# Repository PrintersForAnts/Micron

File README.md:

## Micron R1

# [Printed Part Configurator](https://micron.wizards-enclave.net/) 
<p align="center">
   &nbsp;
   &nbsp;
   &nbsp;
   &nbsp;
  <a aria-label="Discord" href="">

</p>

[The official Micron BOM is here.](https://docs.google.com/spreadsheets/d/1caKSc-EukVpRgN67_by_hdzVPlExSRQ66j3OXlEmcCU)

If you want to purchase full kits there are 3 available (Kits are slowly updating to R1 hardware just make sure to double check the included hardware in your kit and if you have any questions reach out in the discord) 

## LDO Motors Kit 
### US Vendors
[Fabreeko](https://www.fabreeko.com/products/ldo-micron-3d-printer-kit-180mm-3d-printer-kit-with-honeybadger-upgrades)

[KB3D](https://kb-3d.com/store/shop-full-build-kits/6567-ldo-micron-r1-3d-printer-build-kit-by-hartk-6975415159954.html)

[West3d](https://west3d.com/products/ldo-micron-3d-printer-kit-micron-plus-180?_pos=1&_sid=03fbc1c81&_ss=r)

### Non US Vendors

[onetwo3d](https://www.onetwo3d.co.uk/product/ldo-micron-r1-diy-kit/?srsltid=AfmBOoraRNvGTTXXeaEX4yjF97ePEQ5GCPq-xmhn3iUpy0nTGUWonMrJ)

[Zen3d](https://shop.zen3d.eu/ldo-micronplus-r1-kit-black)

## Formbot 3d Kit 
<a href="https://www.formbot3d.com/products/voron-micron-r1-180mm-high-quality-corexy-3d-printer-kit-latest-version?DIST=Rk9OHl4%3D" rel="nofollow">Formbot Micron+ (180x180) Kit (Affiliate Link)</a>

<a href="https://s.click.aliexpress.com/e/_DBn6Ptd" rel="sponsored">Funssor Micron (120x120) Kit (Affiliate Link)</a>

<a href="https://s.click.aliexpress.com/e/_DDDUFkF" rel="nofollow">Formbot Micron+ (180x180) Kit (Aliexpress Affiliate Link)</a>

## [R1 Change Log](https://github.com/PrintersForAnts/Micron/blob/main/R1_changeLog.md)

<details> 
   <summary>
    120x120 build
    </summary>

## Frame Extrusions
Misumi Part #  |Qty | Notes
 ----|----|----|
HFS3-1515-300 |4 | Blind holes need to be drilled
HFS3-1515-220 |10| Ends need to be tapped (M3)
HFS3-1515-205 |2 |
HFS3-1515-190 |1 |
HFS3-1515-120 |1 |

## Linear Rails
Part  | Qty | Length | Notes
-----|----|----|----|
MGN7H | 6 | 160mm | will work with V0 150mm rails if wanted, but 160mm will work as well and is recommended  
MGN9C OR MGN9H | 1 | 160mm | will work V0 150mm rails but 160 will work as well and is recommended 
</details>

<details>
    <summary>
    180x180 build
    </summary>
    
## Frame Extrusions
Misumi Part #  |Qty | Notes
 ----|----|----|
HFS3-1515-350 |4 | Blind holes need to be drilled
HFS3-1515-280 |10| Ends need to be tapped (M3)
HFS3-1515-265 |2 |
HFS3-1515-250 |1 |
HFS3-1515-180 |1 |

## Linear Rails
Part  | Qty | Length
-----|-----|-----|
MGN7H | 6 | 220mm
MGN9C OR MGN9H | 1 | 220mm 
</details>

## No Drop Nuts
There are 2 versions of this mod, 1 from [Zruncho](https://github.com/VoronDesign/VoronUsers/tree/master/printer_mods/zruncho/V0_No_Drop_Nuts) and the other from a user named [Zen3D](https://github.com/VoronDesign/VoronUsers/tree/master/printer_mods/Zen3D/V0_1515_T-nut/). Both of them have their uses. I prefer to use the Zen3D kind just for the fact that the screw can go all the way through the printed part. Zrunchos do have a much nicer fitment into the extrusions but they also dont allow the screw to go all the way through. **NOTE:** the Zruncho nuts will not fit anywhere that has a tab to index to the extrusion - this includes the A/B drives, all idlers, and skirts. If you want to print only one type of nut, use the Zen3d nuts.

## Thank you
Thanks to the following people on Discord who have helped make this printer what it is today. 

- [@KyleGB](https://github.com/Jadecky) - too many additions to name them all
- @TheWarolf#1247
- @L.e.o.p.a.r.d#0990
- @deepfriedheroin#5006
- @JosAr#0517
- @sentein#3903
- @madcat#7838
- @Kyrios#5486
- @faithblinded#1491
- @zruncho#1790
- @Finn#2449
- @clee#1337
- @slidr#4412
- @gfunnymoney#3748
- Jason from LDO
- Voron Dev Team
- all the R1 beta testers
  
[You can support the Micron project on Patreon](https://www.patreon.com/user?u=27661824&fan_landing=true).

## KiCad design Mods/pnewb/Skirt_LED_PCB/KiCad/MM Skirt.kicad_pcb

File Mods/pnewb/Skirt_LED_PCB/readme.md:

# Micron Skirt LEDs #

# Disclaimer #
 This is baby's first PCB.  I have no clue what I'm doing, and take no responsibility if things go pear shaped.  That being said, the KiCad is all in the KiCad folder, along with a zip of the Gerbers that you'd drop onto JLCPCB to make an order.  
 
 Also they're made with the WS2812B-V5 in mind.  These have the decoupling capacitors built in.  If you use the standard issue, probably it'll be fine, maybe a light glitches every now and again, or maybe the first in the chain dies sooner.  Dunno.  As stated above, I have no idea what I'm doing.  `Lab_in_a_lab_coat.jpg`.

Insert the Diffuser and Light blocker into the main body

Slide the PCB in the grooves along the edge

# Sample Config # 
This assumes you're using the optional pass-through to chain from one board into the second.

    [neopixel Skirt_LEDs]
    pin:RGB_PIN
    chain_count: 16
    color_order: GRB
    initial_RED:0.6
    initial_GREEN: 0.6
    initial_BLUE: 0.6

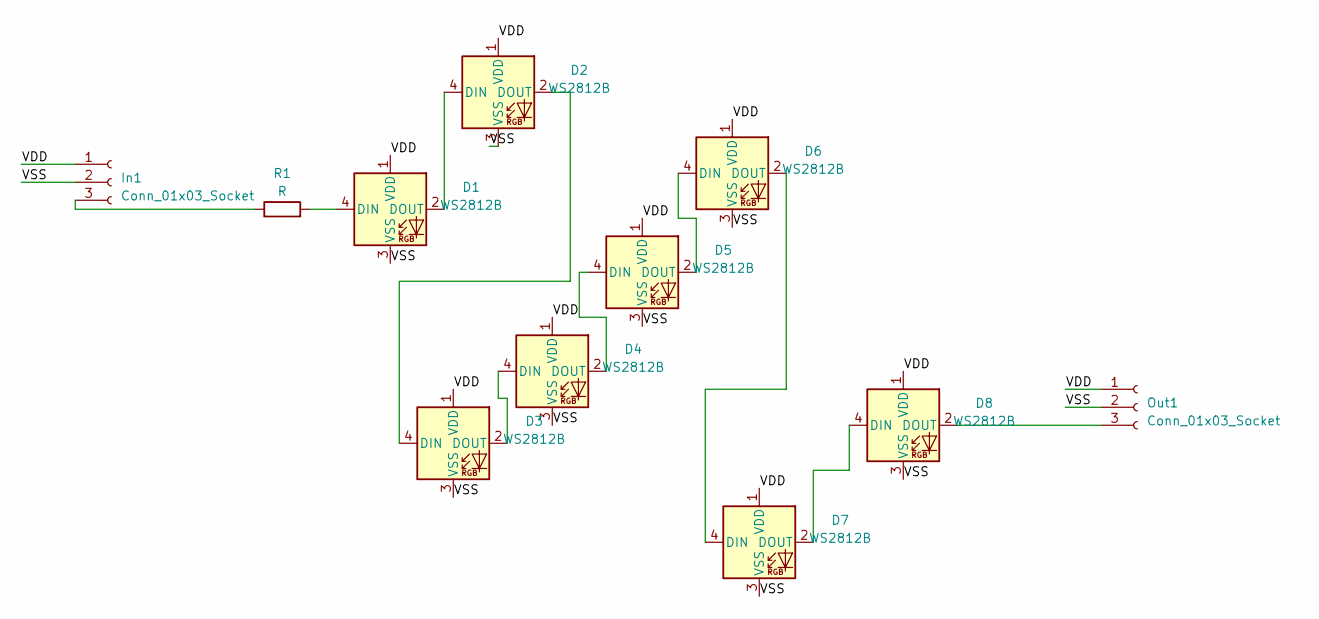
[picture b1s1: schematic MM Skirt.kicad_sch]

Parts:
D1, D2, D3, D4, D5, D6, D7, D8: WS2812B; LED_WS2812B_PLCC4_5.0x5.0mm_P3.2mm
In1: Conn_01x03_Socket; JST_XH_B3B-XH-A_1x03_P2.50mm_Vertical
Out1: Conn_01x03_Socket; JST_XH_B3B-XH-A_1x03_P2.50mm_Vertical
R1: R; R_1206_3216Metric

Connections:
/VDD: D1.1 (VDD), D2.1 (VDD), D3.1 (VDD), D4.1 (VDD), D5.1 (VDD), D6.1 (VDD), D7.1 (VDD), D8.1 (VDD), In1.1, Out1.1
/VSS: D1.3 (VSS), D2.3 (VSS), D3.3 (VSS), D4.3 (VSS), D5.3 (VSS), D6.3 (VSS), D7.3 (VSS), D8.3 (VSS), In1.2, Out1.2
unnamed: D1.4 (DIN), R1.2
unnamed: D1.2 (DOUT), D2.4 (DIN)
unnamed: D2.2 (DOUT), D3.4 (DIN)
unnamed: D3.2 (DOUT), D4.4 (DIN)
unnamed: D4.2 (DOUT), D5.4 (DIN)
unnamed: D5.2 (DOUT), D6.4 (DIN)
unnamed: D6.2 (DOUT), D7.4 (DIN)
unnamed: D7.2 (DOUT), D8.4 (DIN)
unnamed: D8.2 (DOUT), Out1.3
unnamed: In1.3, R1.1

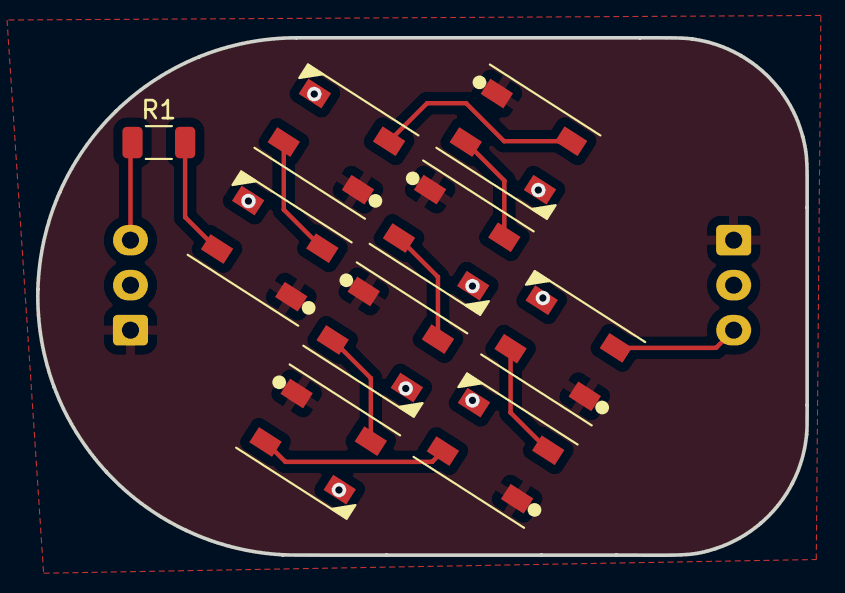
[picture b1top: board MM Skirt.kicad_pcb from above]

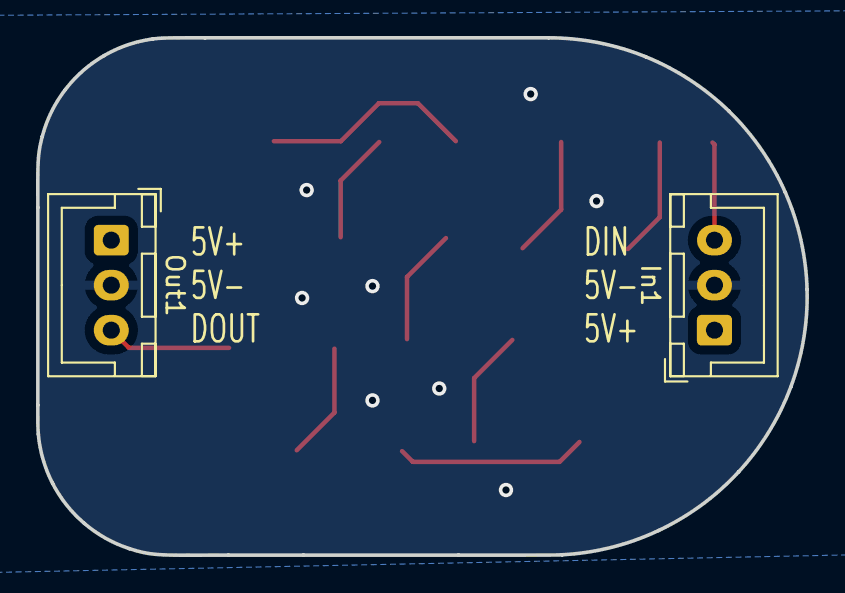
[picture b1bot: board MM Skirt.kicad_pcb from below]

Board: 2 copper layers, 42.7 x 28.7 mm, 11 parts (2 on the bottom side), 12 nets.

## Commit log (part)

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2022-12-18 Delete Mods/clee/Micron+/STLs directory
    no longer needed
2023-01-08 added miniSB, moved miniAB to its own folder
2023-01-08 Re uploading this as it somehow got deleted
2023-01-09 orientation fixed
2023-01-10 updated assembly with miniSB
2023-01-25 updated rail stops to be thicker to fit m3x8s better
2023-03-01 added new render , added cad for slotted fan skirts, updated the fan grills
2023-03-03 updated CAD assembly and fixed naming of some of the STLs
2023-03-18 new gantry , fixed minor alignment issues
2023-03-20 organized waveshare / slotted skirts mod
2023-03-24 updated XY joints belt alignment issues, added alignment tabs on extra a drive upper frame pieces
    fixes issue https://github.com/PrintersForAnts/Micron/issues/89
2023-03-26 updated pin mod for newest gantry fix
2023-03-27 updated XY joints and front idlers
2023-03-27 fixed a drive uppers and orientation on b drive lower pinned
2023-05-01 Various updates
    fixed the alignment of the Z drive gt2 16pulley (moved it over 1.2mm) and adjusted printed spacers to match (3.4mm change to 4.6mm, and 2.2mm change to 1mm)
    fixed the screw holes in the XY Joints Lower Left and Right
    added updated CAD assembly in both .F3D and .Step
2023-05-04 latest fix for XY joints to move bearings in and get belt aligned properly
2023-05-19 fixed probe mount to work with m3x16s better, added z drive spacers for different pulley setups
2023-05-27 organized my mods
2023-05-27 updated pin xy left lower joint
2023-05-31 update before making PR to main branch
2023-06-05 handles added to main cad assembly and stls
2023-06-05 fixed hole size for stepper mounting on lower A and B drive
2023-07-07 Added Bed Fan Mount for Micon+
2023-07-07 Add thumbnail for CAD/PFA_MiniSB_Cowling
2023-07-25 Add MiniSB R1 CAD
2023-07-28 Add Micron+ mini12864 mounting options mod
2023-08-05 Fixed undersized outer pin hole on A Drive Lower
    Outer bearing stack hole for pin mod was undersized compared to other pin mod holes.
    Removed chamfer, pulled hole from 1.40 mm to 1.65mm to achieve the correct 3.30mm diameter and re-added a 0.4mm chamfer.
    Also renamed the bodies on the CAD for the A Drive Upper part, to reflect the Umbilical sizes, hopefully I got these correct!!
2023-08-05 Fix for undersized hole on A Drive Frame Lower
    The hole for the double bearing stack on the Lower part of the A Drive Frame was undersized compared to other holes for the pin mod.
    Removed chamfer, pulled the hole from 1.40mm to 1.65mm to create the correct sized hole, then re-added the 0.4mm chamfer.
    STL & CAD updated, CAD also has A Drive Frame Upper bodies renamed to better reflect the various umbilical mount sizings.
2023-09-13 Update README.md
    updated 120 rear gantry frame piece to the correct 120mm instead of 125mm
2023-09-15 G2Z Beta STL files uploaded
2023-10-22 G2Z Beta r2 update
2023-10-23 added missing bridgdd hole
2023-10-26 fixed G2Z drive mount files that were getting hit by the m3 fhcs
2023-10-29 opened up hole for rear bearing so its easier to remove if needed
2023-11-06 WIP manual updated
2023-11-07 properly named spacers for Z assembly
2023-11-13 added R1 Gantry beta files
2023-11-15 updated R1 gantry files
    added updated XY joints, new AB drive uppers, front Idler bodies, new Hex Z joints
2023-11-15 fixed printing orientation
2023-11-17 fixed bearing screw holes sizes
2023-11-29 R1 Gantry new files update
    PG9 , YC8 umbilical mounts
    lower z chain mount
    z chain guide with thermistor
2023-12-21 assembly pics uploaded
2023-12-21 Adding some flavor to the readme, and all the kicad stuff.
2023-12-31 Create Mini Stealthburner Micron Hex
2024-01-22 R1 gantry pieces updated
    Was messing with making belt different belt paths helping someone model teeth for a gantry and I noticed I messed up on the bearing stacks for the gantry on R1
    I made the pitch line diameter for the belt to follow 10.376mm it should be 10.752 ...Its supposed to be
    2*(R+.376)
    I did (2*R)+.376
    .376 is the value from the smooth side of the belt to the pitch line of the belt
    So this makes it so the belt in CAD that is wrapped around the bearing not exactly where it's supposed to be
2024-01-23 Create Beta_R1_Gantry.step
    uploaded beta .STEP file CAD assembly of the R1 Gantry
2024-01-25 added pinned idlers/bearings for R1 gantry for XY joints and AB drives
2024-01-26 updated X endstop location to fit R1 and added dedicated sensorless X endstop bumpter
2024-01-26 added latest cad for R1 gantry
2024-01-27 minor adjustments and added pinned XY joints CAD
2024-02-01 fixed naming and orientation of the m2 nut adapters
2024-02-05 added R1 BZI Idlers
    these support both Toothed idlers AND bearing stacks
2024-02-07 fixed XY joints, renamed folder names
2024-02-08 fixed xy pinned joints
2024-02-08 updated CAD assembly
2024-02-22 new door parts uploaded and fixed some probe mounts
2024-02-24 updated holes in the hinges , screws were a bit loose
2024-03-09 nema14 Z motor mount added, CAD updated with Z drives , small change to the Z drives (cosmetic only)
2024-03-13 updated cad with the latest front idler changes
2024-03-16 added z idlers and fixed gantry alignment in R1 beta cad assembly
2024-03-19 updated G2Z to fit ring gear better
2024-03-25 uploaded G2Z cad file
2024-03-25 Fix path to G2Z Micron Image after directory renaming
2024-04-05 Rename Z_Idler Tensioner, Add Mirrored Tensioner stl
2024-04-05 latest R1 Z drives Rev 3
2024-04-06 added motor mounts
2024-05-02 3010 side fans mods
2024-05-06 fixes multiple issues
    Fixes #115, #116, #117 , #118
    update cad assembly with all latest changes as well
2024-05-07 Added 3010 bedfans
2024-05-07 Fixed print orientation in STL files
    I dont know how change this in STEP file sorry, but STL are oriented correctly.
2024-05-07 updated klicky dock to include ziptie mounts on the back as well as fixed the height
2024-05-14 updated z tensionor bearing housing overhang
2024-05-21 updated Z drives
    fixed issue #122
    fixed issue #124
2024-05-21 updated Z drives, Fixed #122 and Fixed #124
    fixed issue #122
    fixed issue #124
2024-06-18 side skirts and 4.3 waveshare beta files uploaded
2024-06-19 updates display mount for R1
2024-07-02 Fixed #126 Fixed #128
    added G2Z hula feet adapters
    R1Z hula feet adapters
    updated R1Z drives
    added skirts (side and front waveshare/btt display mount) cad files
    updated the main R1 cad assembly to the latest version
2024-07-08 organized skirts into 120 and 180 folders added the 120 sized side skirts as well as 120 z drive/skirt cad assembly
2024-07-09 added 120x120 R1 cad assembly and rear skirt for 120x120 builds
2024-07-15 added beacon probe mount
2024-07-25 added twist lock panel clips for 3mm foam and panels, fixed orientation of rail stops and an umbilical mount
2024-07-27 Skirts and bottom panel update
    * Updated R1 Skirts to now include accent strips along the bottom as well as allow for a bottom panel to fit
    * Updated skirts to they are all the same height , some had about ~1mm difference between them
    * Updated the waveshare mount to now us m2 self tapping screws instead of filament to keep bezel on
    * Updated Z drive foot mount to accommodate bottom panel
2024-08-01 minor changes to the Z drive for better printability , added filter from KyleGB to main cad assembly
2024-08-02 organized panelclip files, updated cad assembly with all the latest changes
2024-08-11 adding initial printer-cfg for manta m8p v2
2024-08-24 Additional QOL mods by G
2024-08-24 Fixed README urls for G mods
2024-08-24 Added step files and corrected part orientations
2024-08-25 Image folder typo
2024-09-03 cleaned up cad, added filter stls, renamed various stls
2024-09-06 cleaned up CAD and adjusted gantry files
    * cleaned up main cad assembly
    * posted link to fusion source assembly file to be downloaded
    * adjusted gantry files to no longer need built in printed shim, now there are shims on both sides of every bearing stack
2024-09-10 added double shear bearing mounts
2024-09-12 updated umblical mounts to work with top bearing mounts
2024-09-18 fixed counterbore bridging on the rear bowden entry files , updated cad assembly, removed all redundant files in the cad assembly
2024-09-21 updated the front idlers to increase tension travel distance from 3mm to 8mm , updated cad assembly with latest idlers
    carrier and covers dont need a reprint , just the housing
2024-09-26 added g2z skirts and skinny twist lock key
2024-10-09 updated probe mounts to work with anthead latest changes
2024-10-18 updated R1 , view readme for changelog
2024-10-18 fixed issues with fan grill and side skirt accents
2024-11-07 Revert "added 12mm no drop nuts for formbot kit and archetype BB klicky dock"
    This reverts commit c38844a607a66c36feb0da10ba75567cfcd2e76f.
2024-11-07 Reapply "added 12mm no drop nuts for formbot kit and archetype BB klicky dock"
    This reverts commit ba13055ebba6fd9d81fa06e47def2f959a31c88d.
2024-11-19 moved to MOD folder per request
2024-11-22 added bottom panel drilling jig, xy joints with live idlers, latest cad V68 , renamed xy joint files
2024-11-27 fixes #139
2025-01-11 Create Foof mod folder
    Create Foof mod folder
2025-01-11 Added Z Drive mod for Powge 60T pulleys
    Added Z Drive mod for Powge 60T pulleys
2025-01-20 fixed #143 , fixed #141, fixed #138 , fixed #137
    organized cad, fixed various issues
    #143 , #141, #138 , #137
2025-02-05 fixed missing parts in cad assembly
2025-02-10 rename folder
2025-02-10 Move Firmware/Slicer/BedModel to Slicer_Profiles/BedModel
2025-02-10 Add OrcaSlicer Profile
2025-03-03 Fixed #148, Fixed #149
    added parametric panel clips cad file
    fixed wrong hardware in front idlers,
    fixed miss aligned heatsets in Z drives
    added m5 shims/washers to z drive shaft assembly
    simplified the anthead cad to be a default option if you want the rest of the cad its in the https://www.github.com/PrintersForAnts/AntHead repo
2025-04-16 Update R1_changeLog.md
    fixed date formatting on the change log
2025-04-16 fan mounts updated screw holes to fit m3x16 screws
2025-04-16 fixed and renamed the bed fan wago mount
2025-04-17 removing old electronics brackets and adding and organizing new mounts for various 8 driver boards and raspi
2025-04-21 fixed blank keystone insert and updated rear skirt (adamstech inlet) to give more room for wiring
2025-04-25 fixed minor chamfer that was missing
2025-05-29 updated bed fans to have hexagon grill inserts fixed #163
2025-06-04 updated bed fans with grills to fit 5015s properly
2025-07-08 fixed #145 , fixed #166 , fixed #180 , fixed #181
    also added pinned z idlers to match the rest of the printer having pinned versions as well
2025-07-10 Rename BTTMantaM8P.cfg to BTTMantaM8P_v1-1.cfg
2025-07-10 Update printer.cfg
    updated to include manta v2
2025-07-23 fix usermods readme
    removed removed Micron+
    fixed all links to be relative - some were broken
    added trailing pipes in markdown table
2025-08-02 Update x_carriage_mgn9h_x1.stl , fixed issue with anthead fans hitting the carriage as well as the offset between the probe mounts and the face of the carriage
    offset was 4.57mm it should be 5mm
2025-08-14 config updates
    adjusted m8pv2 cfg motor aliases to use _UART instead of _CS.
    printer.cfg updated to move ADXL pins to thb, and add thb mcu temperature sensor.
2025-08-14 config updates (#188)
    * config updates
    adjusted m8pv2 cfg motor aliases to use _UART instead of _CS.
    printer.cfg updated to move ADXL pins to thb, and add thb mcu temperature sensor.
    * v1-1 and additional v2 corrections
2025-08-20 added boop and pzprobe cfg options (#189)
    * Create boop.cfg
    * Create pzprobe.cfg
    * Update printer.cfg
2025-09-09 replaced the screwed on panel clips with the correct STLs
2025-10-07 fixed #190 , fixed #184 , fixed #146
    updated latest cad assembly
    added some various files to the mods folders
2025-11-01 fixed #190, fixed #146
2025-12-02 added specific micron Kit section in the STLs folder
2025-12-02 Update README with LDO Motors and Formbot kits
    Added sections for LDO Motors Kit and Formbot 3D Kit with vendor links.
2025-12-02 renamed files
2025-12-31 Add note about nut compatibility
2025-12-31 Type on type
2026-01-03 Fix pins to match LDO wiring instructions
2026-01-30 Create cartov4.cfg
    updated config for changes to the v4 cartographer probe that differ from version 3
